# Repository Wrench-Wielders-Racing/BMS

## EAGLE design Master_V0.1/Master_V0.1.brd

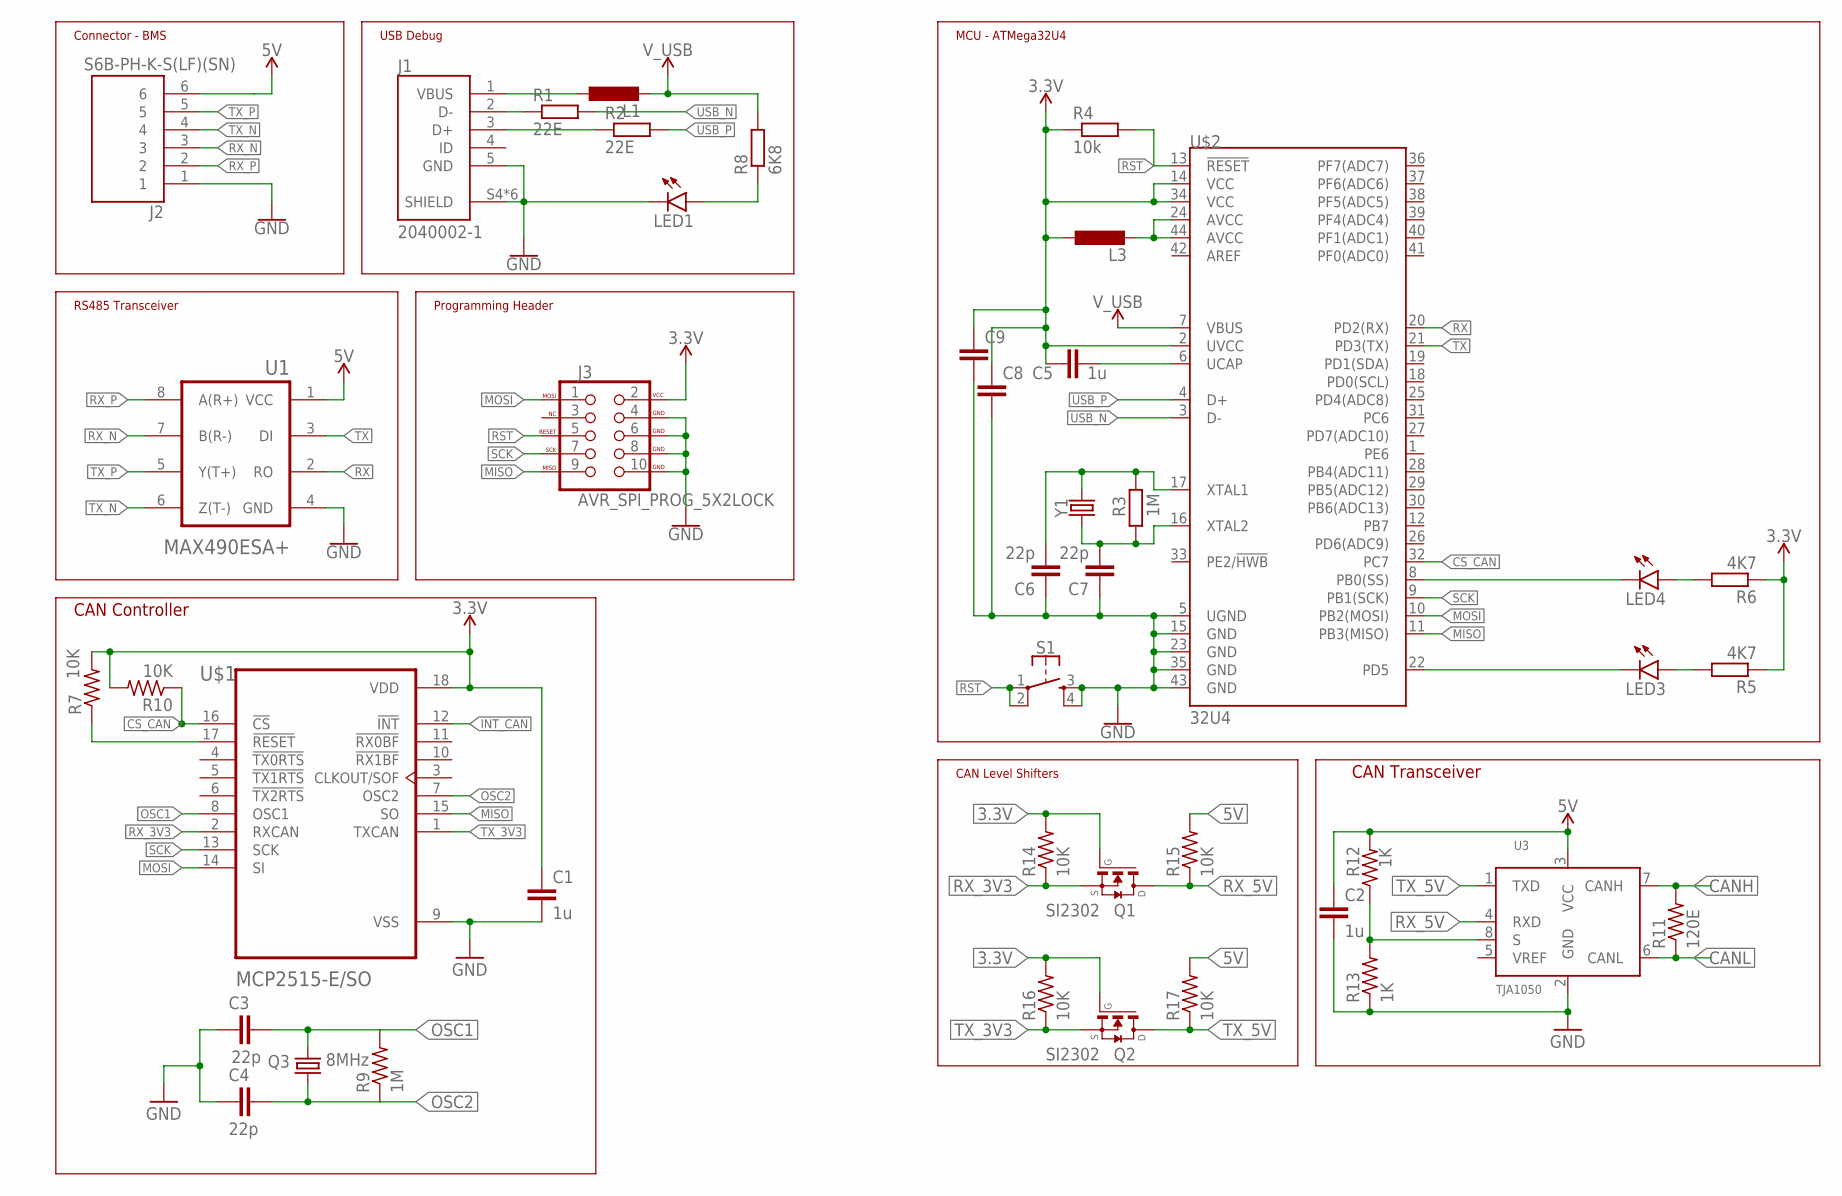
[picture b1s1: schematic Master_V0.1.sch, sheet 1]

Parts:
C1, C2, C5: 1u; C0805
C3, C4, C6, C7: 22p; C0805
C8, C9: C-EUC0805; C0805
J1: 2040002-1; TE_2040002-1
J2: S6B-PH-K-S(LF)(SN); JST_S6B-PH-K-S(LF)(SN)
J3: AVR_SPI_PROG_5X2LOCK; 2X5-SHROUDED_LOCK
L1, L3: L-EUL2012C; L2012C
LED1, LED3, LED4: LEDCHIPLED_0805; CHIPLED_0805
Q1, Q2: SI2302; SOT23
Q3: 8MHz; HC49/S
R1, R2: 22E; R0805
R3, R9: 1M; R0805
R4: 10k; R0805
R5, R6: 4K7; R0805
R7, R10, R14, R15, R16, R17: 10K; R0805
R8: 6K8; R0805
R11: 120E; R0805
R12, R13: 1K; R0805
S1: MOMENTARY-SWITCH-SPST-2-SMD-5.2MM; TACTILE_SWITCH_SMD_5.2MM
U1: MAX490ESA+; SOIC127P600X175-8N
U3: TJA1050; SOT96-1
U$1: MCP2515-E/SO; SOIC127P1030X265-18N
U$2: 32U4; TQFP44
Y1: CRYSTALPTH-HC49UV; HC49U

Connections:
3.3V: C1.1, C5.1, C8.1, C9.1, J3.2 (VCC), L3.1, Q1.1 (G), Q2.1 (G), R4.1, R5.1, R6.1, R7.2, R10.2, R14.2, R16.2, U$1.18 (VDD), U$2.2 (UVCC), U$2.14 (VCC), U$2.34 (VCC); also elsewhere on the board
5V: C2.1, J2.6, R12.2, R15.2, R17.2, U1.1 (VCC), U3.3 (VCC); also elsewhere on the board
CANH: R11.2, U3.7 (CANH); also elsewhere on the board
CANL: R11.1, U3.6 (CANL); also elsewhere on the board
CS_CAN: R10.1, U$1.16 (!CS), U$2.32 (PC7)
GND: C1.2, C2.2, C3.1, C4.1, C6.1, C7.1, C8.2, C9.2, J1.5 (GND), J1.S4 (SHIELD), J1.S5 (SHIELD), J1.SH1 (SHIELD), J1.SH2 (SHIELD), J1.SH3 (SHIELD), J1.SH4 (SHIELD), J2.1, J3.4 (GND), J3.6 (GND), J3.8 (GND), J3.10 (GND), LED1.C, R13.1, S1.3, S1.4, U1.4 (GND), U3.2 (GND), U$1.9 (VSS), U$2.5 (UGND), U$2.15 (GND), U$2.23 (GND), U$2.35 (GND), U$2.43 (GND); also elsewhere on the board
INT_CAN: U$1.12 (!INT)
MISO: J3.9 (MISO), U$1.15 (SO), U$2.11 (PB3(MISO))
MOSI: J3.1 (MOSI), U$1.14 (SI), U$2.10 (PB2(MOSI))
unnamed: J1.3 (D+), R2.1
unnamed: J1.2 (D-), R1.1
unnamed: J1.1 (VBUS), L1.1
unnamed: L3.2, U$2.24 (AVCC), U$2.44 (AVCC)
unnamed: LED1.A, R8.1
unnamed: R7.1, U$1.17 (!RESET)
unnamed: C5.2, U$2.6 (UCAP)
unnamed: LED3.C, U$2.22 (PD5)
unnamed: C6.2, R3.2, U$2.17 (XTAL1), Y1.2
unnamed: LED3.A, R5.2
unnamed: C7.2, R3.1, U$2.16 (XTAL2), Y1.1
unnamed: LED4.C, U$2.8 (PB0(SS))
unnamed: LED4.A, R6.2
unnamed: R12.1, R13.2, U3.8 (S)
OSC1: C3.2, Q3.2, R9.2, U$1.8 (OSC1)
OSC2: C4.2, Q3.1, R9.1, U$1.7 (OSC2)
RST: J3.5 (RESET), R4.2, S1.1, S1.2, U$2.13 (!RESET)
RX: U1.2 (RO), U$2.20 (PD2(RX))
RX_3V3: Q1.2 (S), R14.1, U$1.2 (RXCAN)
RX_5V: Q1.3 (D), R15.1, U3.4 (RXD)
RX_N: J2.3, U1.7 (B(R-))
RX_P: J2.2, U1.8 (A(R+))
SCK: J3.7 (SCK), U$1.13 (SCK), U$2.9 (PB1(SCK))
TX: U1.3 (DI), U$2.21 (PD3(TX))
TX_3V3: Q2.2 (S), R16.1, U$1.1 (TXCAN)
TX_5V: Q2.3 (D), R17.1, U3.1 (TXD)
TX_N: J2.4, U1.6 (Z(T-))
TX_P: J2.5, U1.5 (Y(T+))
USB_N: R1.2, U$2.3 (D-)
USB_P: R2.2, U$2.4 (D+)
V_USB: L1.2, R8.2, U$2.7 (VBUS)

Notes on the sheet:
Connector - BMS
USB Debug
MCU - ATMega32U4
RS485 Transceiver
Programming Header
CAN Transceiver
CAN Controller
CAN Level Shifters

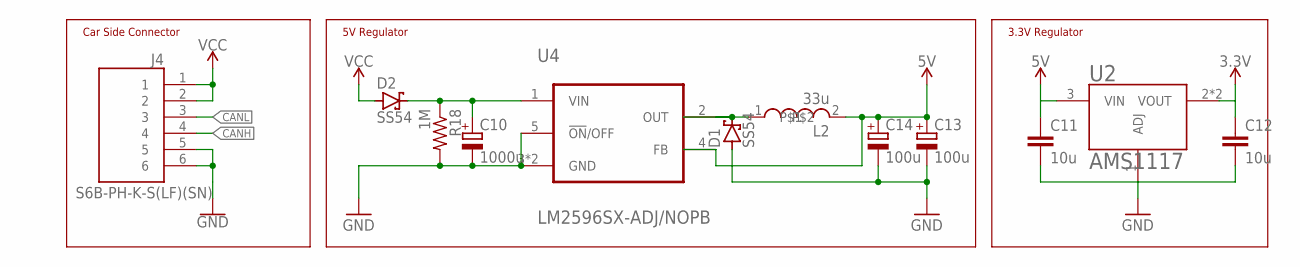
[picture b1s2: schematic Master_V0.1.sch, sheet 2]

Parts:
C10: 1000u; E5-10,5
C11, C12: 10u; C0805
C13, C14: 100u; E2-4
D1, D2: SS54; SMC
J4: S6B-PH-K-S(LF)(SN); JST_S6B-PH-K-S(LF)(SN)
L2: 33u; CDRH127/LD
R18: 1M; R0805
U2: AMS1117; SOT230P700X170-4
U4: LM2596SX-ADJ/NOPB; VREG_LM2596SX-ADJ/NOPB

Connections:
3.3V: C12.1, U2.2 (VOUT), U2.4 (VOUT); also elsewhere on the board
5V: C11.1, C13.+, C14.+, L2.2, U2.3 (VIN), U4.4 (FB); also elsewhere on the board
CANH: J4.4; also elsewhere on the board
CANL: J4.3; also elsewhere on the board
GND: C10.-, C11.2, C12.2, C13.-, C14.-, D1.A, J4.5, J4.6, R18.2, U2.1 (ADJ), U4.3 (GND), U4.5 (!ON!/OFF), U4.6 (GND); also elsewhere on the board
unnamed: D1.C, L2.1, U4.2 (OUT)
unnamed: C10.+, D2.C, R18.1, U4.1 (VIN)
VCC: D2.A, J4.1, J4.2

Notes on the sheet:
Car Side Connector
5V Regulator
3.3V Regulator

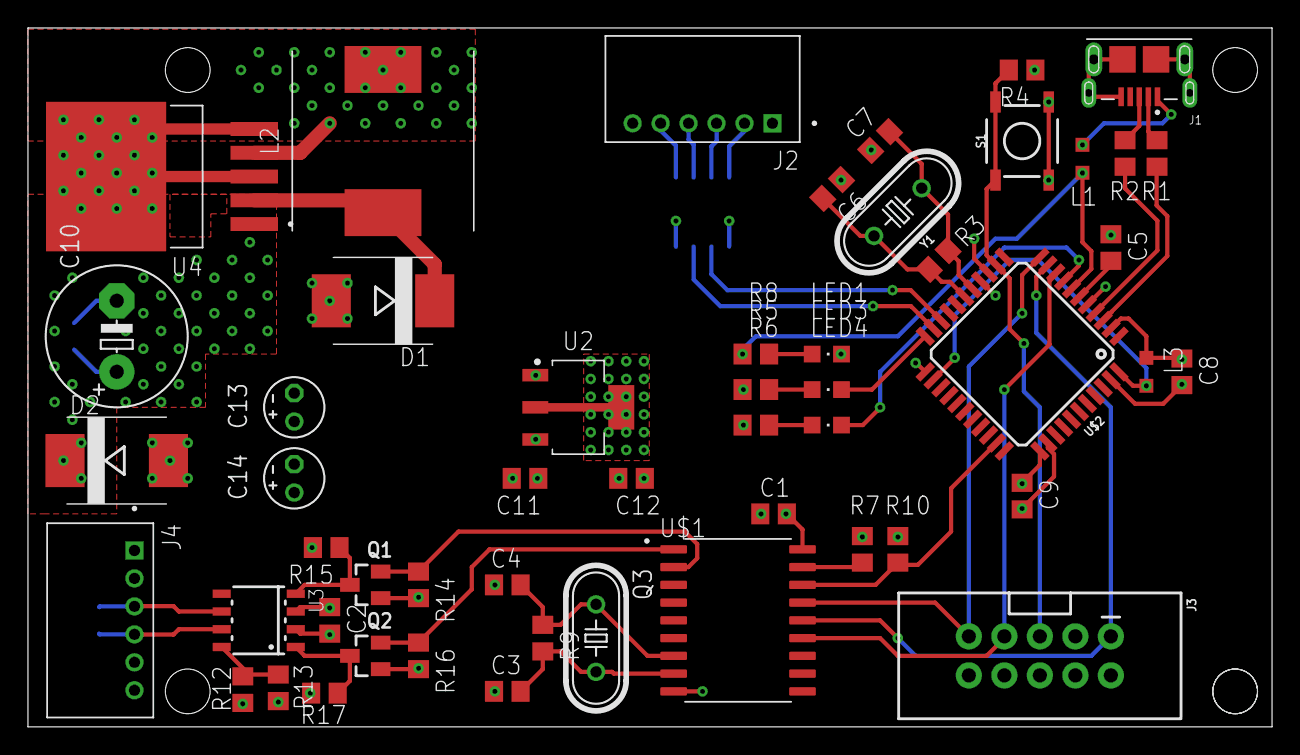
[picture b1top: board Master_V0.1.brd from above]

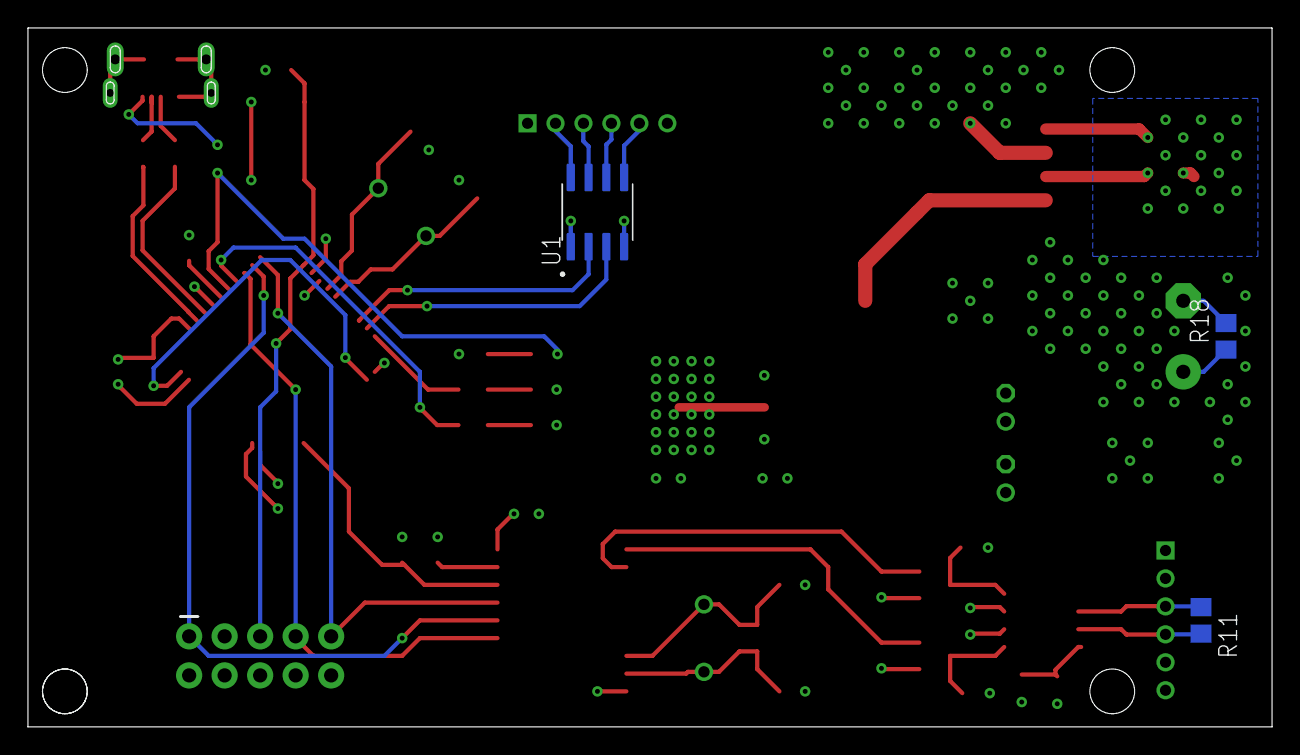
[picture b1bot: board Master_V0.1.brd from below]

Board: 4 copper layers, 89.0 x 50.0 mm, 55 parts (3 on the bottom side), 42 nets.

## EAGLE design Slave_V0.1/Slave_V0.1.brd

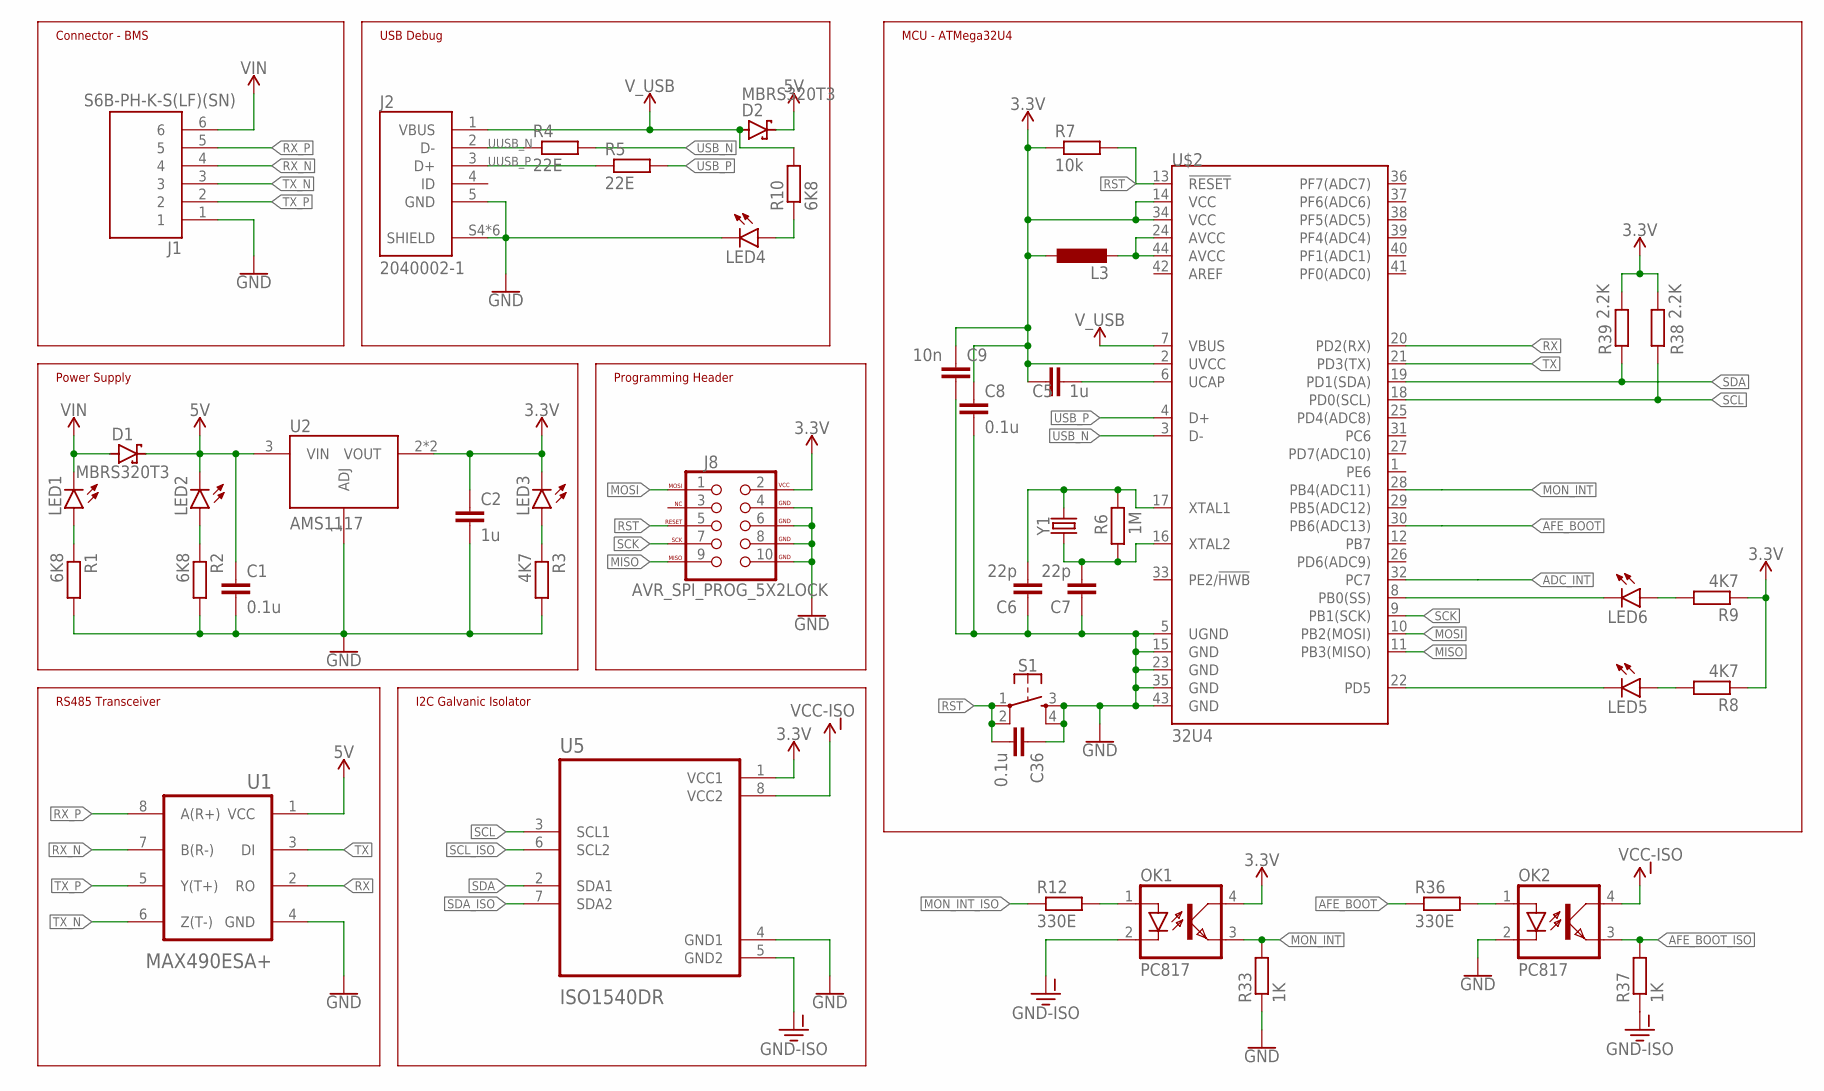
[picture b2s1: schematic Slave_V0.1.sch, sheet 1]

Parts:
C1, C8, C36: 0.1u; C0805
C2, C5: 1u; C0805
C6, C7: 22p; C0805
C9: 10n; C0805
D1, D2: MBRS320T3; SMC
J1: S6B-PH-K-S(LF)(SN); JST_S6B-PH-K-S(LF)(SN)
J2: 2040002-1; TE_2040002-1
J8: AVR_SPI_PROG_5X2LOCK; 2X5-SHROUDED_LOCK
L3: L-EUL2012C; L2012C
LED1, LED2, LED3, LED4, LED5, LED6: LEDCHIPLED_0805; CHIPLED_0805
OK1, OK2: PC817; DIL04
R1, R2, R10: 6K8; R0805
R3, R8, R9: 4K7; R0805
R4, R5: 22E; R0805
R6: 1M; R0805
R7: 10k; R0805
R12, R36: 330E; R0805
R33, R37: 1K; R0805
R38, R39: 2.2K; R0805
S1: MOMENTARY-SWITCH-SPST-2-SMD-5.2MM; TACTILE_SWITCH_SMD_5.2MM
U1: MAX490ESA+; SOIC127P600X175-8N
U2: AMS1117; SOT230P700X170-4
U5: ISO1540DR; SOIC127P599X175-8N
U$2: 32U4; TQFP44
Y1: CRYSTALPTH-HC49UV; HC49U

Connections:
3.3V: C2.1, C5.1, C8.1, C9.1, J8.2 (VCC), L3.1, LED3.C, OK1.4 (COL), R7.1, R8.1, R9.1, R38.2, R39.2, U2.2 (VOUT), U2.4 (VOUT), U5.1 (VCC1), U$2.2 (UVCC), U$2.14 (VCC), U$2.34 (VCC); also elsewhere on the board
5V: C1.1, D1.C, D2.C, LED2.C, U1.1 (VCC), U2.3 (VIN)
ADC_INT: U$2.32 (PC7); also elsewhere on the board
AFE_BOOT: R36.1, U$2.30 (PB6(ADC13))
AFE_BOOT_ISO: OK2.3 (EMIT), R37.2; also elsewhere on the board
GND: C1.2, C2.2, C6.1, C7.1, C8.2, C9.2, C36.1, J1.1, J2.5 (GND), J2.S4 (SHIELD), J2.S5 (SHIELD), J2.SH1 (SHIELD), J2.SH2 (SHIELD), J2.SH3 (SHIELD), J2.SH4 (SHIELD), J8.4 (GND), J8.6 (GND), J8.8 (GND), J8.10 (GND), LED4.C, OK2.2 (C), R1.2, R2.2, R3.2, R33.1, S1.3, S1.4, U1.4 (GND), U2.1 (ADJ), U5.4 (GND1), U$2.5 (UGND), U$2.15 (GND), U$2.23 (GND), U$2.35 (GND), U$2.43 (GND); also elsewhere on the board
GND-ISO: OK1.2 (C), R37.1, U5.5 (GND2); also elsewhere on the board
MISO: J8.9 (MISO), U$2.11 (PB3(MISO))
MON_INT: OK1.3 (EMIT), R33.2, U$2.28 (PB4(ADC11))
MON_INT_ISO: R12.1; also elsewhere on the board
MOSI: J8.1 (MOSI), U$2.10 (PB2(MOSI))
unnamed: LED1.A, R1.1
unnamed: LED3.A, R3.1
unnamed: LED2.A, R2.1
unnamed: L3.2, U$2.24 (AVCC), U$2.44 (AVCC)
unnamed: C5.2, U$2.6 (UCAP)
unnamed: C6.2, R6.2, U$2.17 (XTAL1), Y1.2
unnamed: LED5.C, U$2.22 (PD5)
unnamed: C7.2, R6.1, U$2.16 (XTAL2), Y1.1
unnamed: LED5.A, R8.2
unnamed: LED6.C, U$2.8 (PB0(SS))
unnamed: LED6.A, R9.2
unnamed: LED4.A, R10.1
unnamed: OK2.1 (A), R36.2
unnamed: OK1.1 (A), R12.2
RST: C36.2, J8.5 (RESET), R7.2, S1.1, S1.2, U$2.13 (!RESET)
RX: U1.2 (RO), U$2.20 (PD2(RX))
RX_N: J1.4, U1.7 (B(R-))
RX_P: J1.5, U1.8 (A(R+))
SCK: J8.7 (SCK), U$2.9 (PB1(SCK))
SCL: R38.1, U5.3 (SCL1), U$2.18 (PD0(SCL)); also elsewhere on the board
SCL_ISO: U5.6 (SCL2); also elsewhere on the board
SDA: R39.1, U5.2 (SDA1), U$2.19 (PD1(SDA)); also elsewhere on the board
SDA_ISO: U5.7 (SDA2); also elsewhere on the board
TX: U1.3 (DI), U$2.21 (PD3(TX))
TX_N: J1.3, U1.6 (Z(T-))
TX_P: J1.2, U1.5 (Y(T+))
USB_N: R4.2, U$2.3 (D-)
USB_P: R5.2, U$2.4 (D+)
UUSB_N: J2.2 (D-), R4.1
UUSB_P: J2.3 (D+), R5.1
VCC-ISO: OK2.4 (COL), U5.8 (VCC2); also elsewhere on the board
VIN: D1.A, J1.6, LED1.C
V_USB: D2.A, J2.1 (VBUS), R10.2, U$2.7 (VBUS)

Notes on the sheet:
Connector - BMS
Power Supply
USB Debug
MCU - ATMega32U4
RS485 Transceiver
I2C Galvanic Isolator
Programming Header

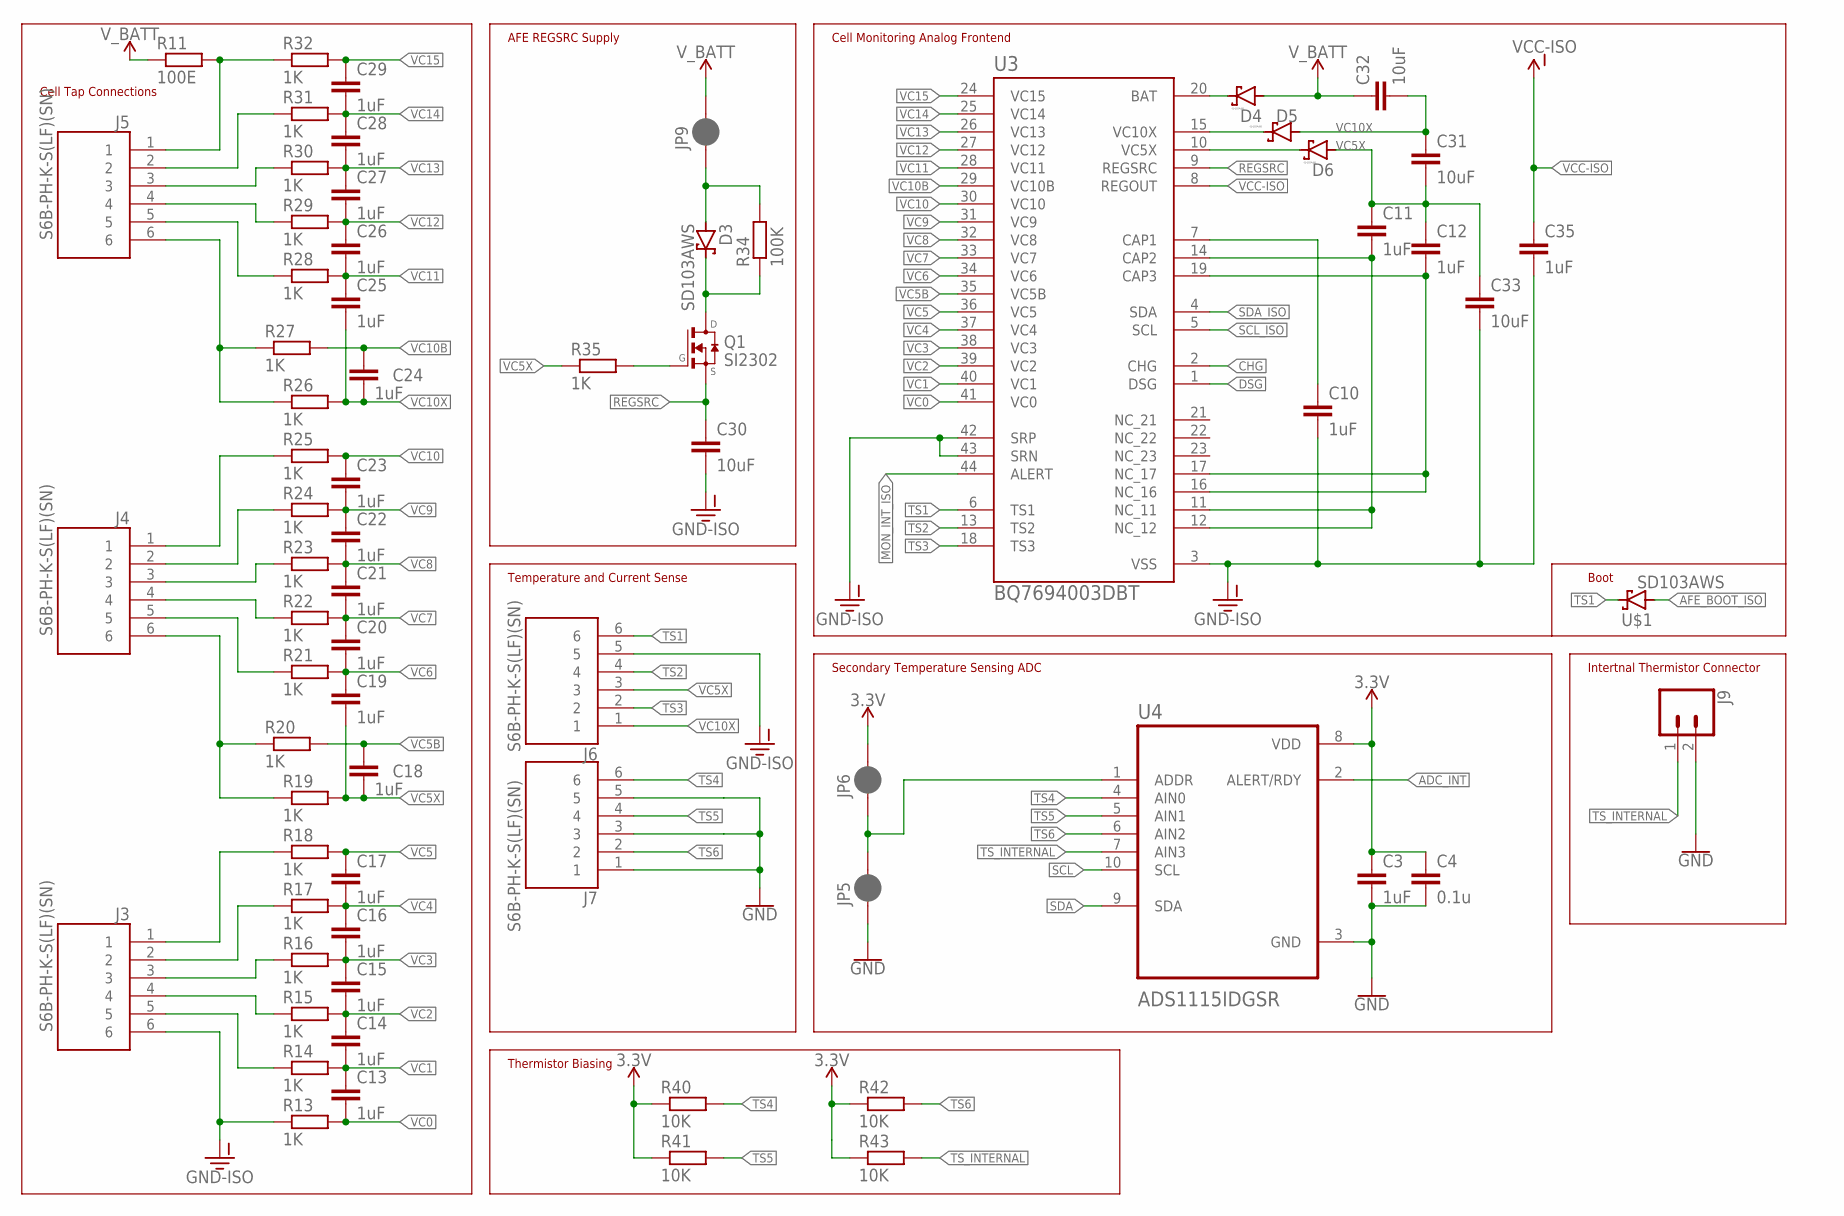
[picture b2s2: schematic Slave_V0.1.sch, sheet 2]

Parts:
C3: 1uF; C0805K
C4: 0.1u; C0805K
C10, C11, C12, C13, C14, C15, C16, C17, C18, C19, C20, C21, C22, C23, C24, C25, C26, C27, C28, C29, C35: 1uF; C0805
C30, C31, C32, C33: 10uF; C0805
D3, D4, D5, D6: SD103AWS; SOD323_ST
J3, J4, J5, J6, J7: S6B-PH-K-S(LF)(SN); JST_S6B-PH-K-S(LF)(SN)
J9: CONN_023.5MM-NO_SILK; SCREWTERMINAL-3.5MM-2-NS
JP5, JP6, JP9: JUMPER-SMT_2_NC_PASTE_SILK; SMT-JUMPER_2_NC_PASTE_SILK
Q1: SI2302; SOT23
R11: 100E; R0805
R13, R14, R15, R16, R17, R18, R19, R20, R21, R22, R23, R24, R25, R26, R27, R28, R29, R30, R31, R32, R35: 1K; R0805
R34: 100K; R0805
R40, R41, R42, R43: 10K; R0805
U3: BQ7694003DBT; SOP50P640X120-44N
U4: ADS1115IDGSR; SOP50P490X110-10N
U$1: SD103AWS; SOD323_ST

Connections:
3.3V: C3.1, C4.1, JP6.2, R40.1, R41.1, R42.1, R43.1, U4.8 (VDD); also elsewhere on the board
ADC_INT: U4.2 (ALERT/RDY); also elsewhere on the board
AFE_BOOT_ISO: U$1.A; also elsewhere on the board
CHG: U3.2 (CHG)
DSG: U3.1 (DSG)
GND: C3.2, C4.2, J7.1, J7.3, J7.5, J9.2, JP5.1, U4.3 (GND); also elsewhere on the board
GND-ISO: C10.2, C30.2, C33.2, C35.2, J3.6, J6.5, R13.1, U3.3 (VSS), U3.42 (SRP), U3.43 (SRN); also elsewhere on the board
MON_INT_ISO: U3.44 (ALERT); also elsewhere on the board
unnamed: JP5.2, JP6.1, U4.1 (ADDR)
unnamed: C10.1, U3.7 (CAP1)
unnamed: C11.2, U3.11 (NC_11), U3.12 (NC_12), U3.14 (CAP2)
unnamed: D3.A, JP9.1, R34.2
unnamed: D3.C, Q1.3 (D), R34.1
unnamed: C12.2, U3.16 (NC_16), U3.17 (NC_17), U3.19 (CAP3)
unnamed: J4.4, R22.1
unnamed: J4.3, R23.1
unnamed: J4.2, R24.1
unnamed: J4.5, R21.1
unnamed: J4.6, R19.1, R20.1
unnamed: J4.1, R25.1
unnamed: J3.4, R15.1
unnamed: J3.3, R16.1
unnamed: J3.2, R17.1
unnamed: J3.5, R14.1
unnamed: J5.4, R29.1
unnamed: J3.1, R18.1
unnamed: J5.3, R30.1
unnamed: J5.2, R31.1
unnamed: J5.5, R28.1
unnamed: J5.6, R26.1, R27.1
unnamed: Q1.1 (G), R35.2
unnamed: J5.1, R11.2, R32.1
unnamed: D4.C, U3.20 (BAT)
unnamed: D5.C, U3.15 (VC10X)
unnamed: D6.C, U3.10 (VC5X)
REGSRC: C30.1, Q1.2 (S), U3.9 (REGSRC)
SCL: U4.10 (SCL); also elsewhere on the board
SCL_ISO: U3.5 (SCL); also elsewhere on the board
SDA: U4.9 (SDA); also elsewhere on the board
SDA_ISO: U3.4 (SDA); also elsewhere on the board
TS1: J6.6, U3.6 (TS1), U$1.C
TS2: J6.4, U3.13 (TS2)
TS3: J6.2, U3.18 (TS3)
TS4: J7.6, R40.2, U4.4 (AIN0)
TS5: J7.4, R41.2, U4.5 (AIN1)
TS6: J7.2, R42.2, U4.6 (AIN2)
TS_INTERNAL: J9.1, R43.2, U4.7 (AIN3)
VC0: C13.2, R13.2, U3.41 (VC0)
VC1: C13.1, C14.2, R14.2, U3.40 (VC1)
VC2: C14.1, C15.2, R15.2, U3.39 (VC2)
VC3: C15.1, C16.2, R16.2, U3.38 (VC3)
VC4: C16.1, C17.2, R17.2, U3.37 (VC4)
VC5: C17.1, R18.2, U3.36 (VC5)
VC5B: C18.1, R20.2, U3.35 (VC5B)
VC5X: C11.1, C12.1, C18.2, C19.2, C31.2, C33.1, D6.A, J6.3, R19.2, R35.1
VC6: C19.1, C20.2, R21.2, U3.34 (VC6)
VC7: C20.1, C21.2, R22.2, U3.33 (VC7)
VC8: C21.1, C22.2, R23.2, U3.32 (VC8)
VC9: C22.1, C23.2, R24.2, U3.31 (VC9)
VC10: C23.1, R25.2, U3.30 (VC10)
VC10B: C24.1, R27.2, U3.29 (VC10B)
VC10X: C24.2, C25.2, C31.1, C32.2, D5.A, J6.1, R26.2
VC11: C25.1, C26.2, R28.2, U3.28 (VC11)
VC12: C26.1, C27.2, R29.2, U3.27 (VC12)
VC13: C27.1, C28.2, R30.2, U3.26 (VC13)
VC14: C28.1, C29.2, R31.2, U3.25 (VC14)
VC15: C29.1, R32.2, U3.24 (VC15)
VCC-ISO: C35.1, U3.8 (REGOUT); also elsewhere on the board
V_BATT: C32.1, D4.A, JP9.2, R11.1

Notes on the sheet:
Cell Tap Connections
AFE REGSRC Supply
Temperature and Current Sense
Cell Monitoring Analog Frontend
Secondary Temperature Sensing ADC
Boot
Thermistor Biasing
Intertnal Thermistor Connector

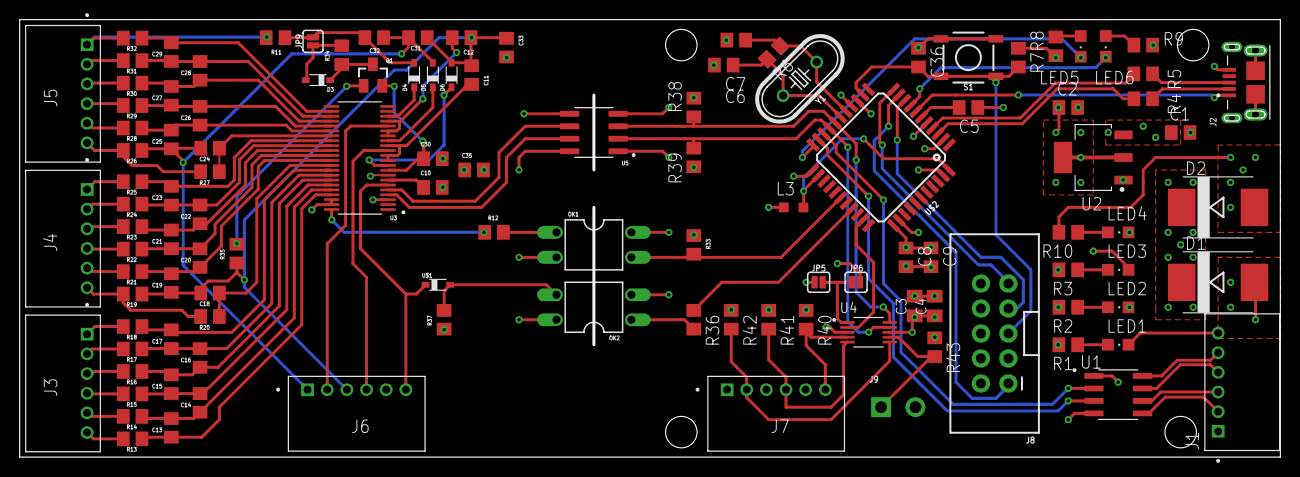
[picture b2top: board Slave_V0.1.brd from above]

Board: 4 copper layers, 127.9 x 44.2 mm, 115 parts (0 on the bottom side), 100 nets.

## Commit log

2020-12-17 Initial overdue commit

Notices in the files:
parts and their libraries:
SparkFun-Connectors: Licensing: Creative Commons ShareAlike 4.0 International - https://creativecommons.org/licenses/by-sa/4.0
